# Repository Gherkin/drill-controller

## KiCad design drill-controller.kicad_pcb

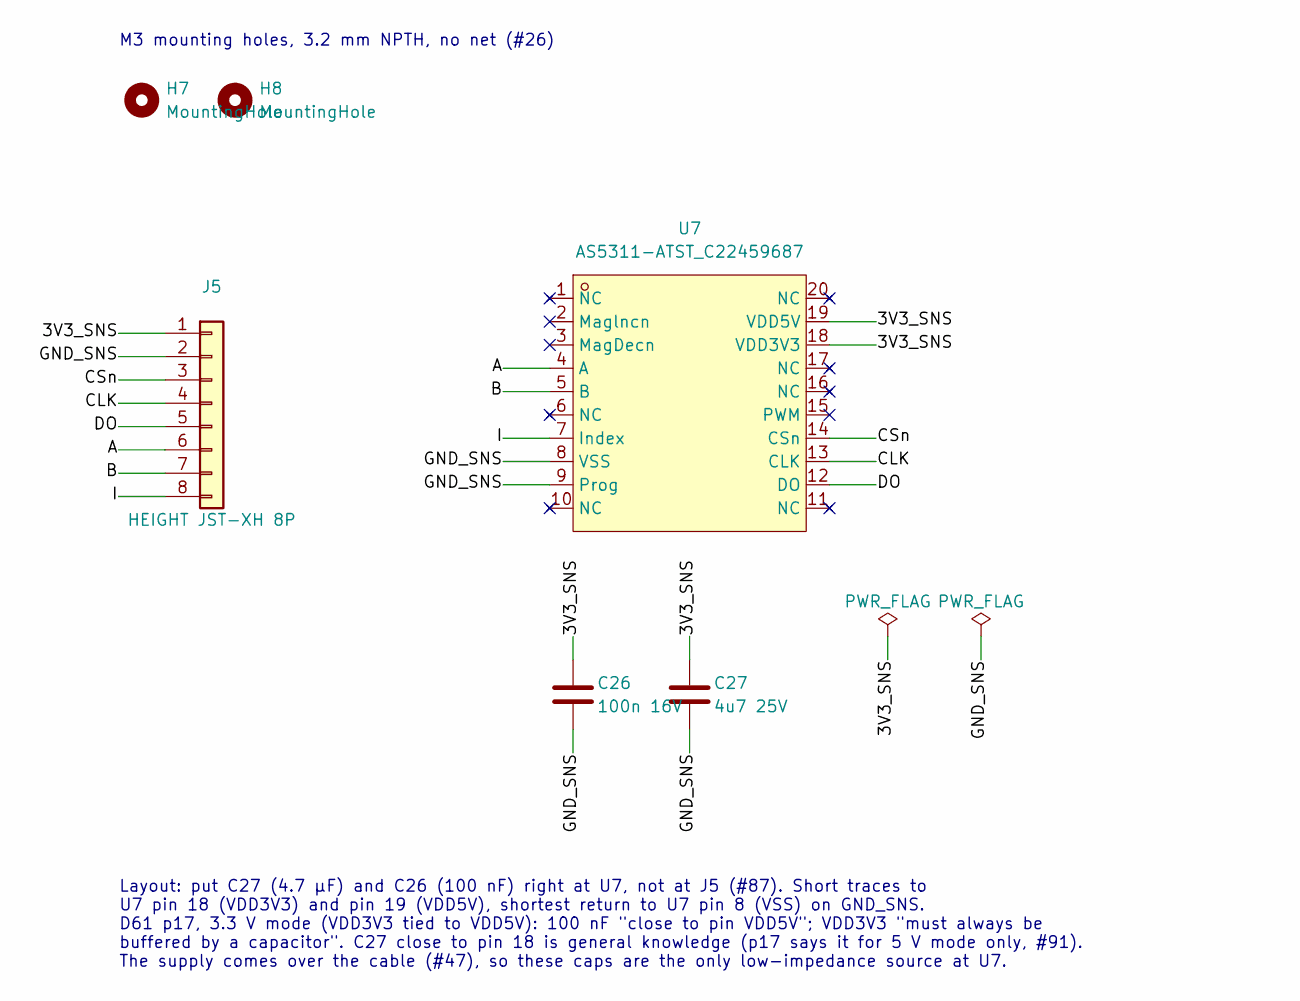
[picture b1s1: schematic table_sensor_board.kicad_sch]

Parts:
C26: 100n 16V; C_0402_1005Metric; LCSC Part C1525
C27: 4u7 25V; C_0805_2012Metric; LCSC Part C1779
H7, H8: MountingHole; MountingHole_3.2mm_M3_ISO14580
J5: HEIGHT JST-XH 8P; CONN-TH_8P-P2.50_B8B-XH-2-LF-SN; LCSC Part C157973
U7: AS5311-ATST_C22459687; TSSOP-20_L6.5-W4.4-P0.65-LS6.4-BL; LCSC Part C22459687

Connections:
/Table Height Sensor Board/3V3_SNS: C26.1, C27.1, J5.1, U7.18 (VDD3V3), U7.19 (VDD5V)
/Table Height Sensor Board/A: J5.6, U7.4 (A)
/Table Height Sensor Board/B: J5.7, U7.5 (B)
/Table Height Sensor Board/CLK: J5.4, U7.13 (CLK)
/Table Height Sensor Board/CSn: J5.3, U7.14 (CSn)
/Table Height Sensor Board/DO: J5.5, U7.12 (DO)
/Table Height Sensor Board/GND_SNS: C26.2, C27.2, J5.2, U7.8 (VSS), U7.9 (Prog)
/Table Height Sensor Board/I: J5.8, U7.7 (Index)

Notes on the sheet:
Layout: put C27 (4.7 µF) and C26 (100 nF) right at U7, not at J5 (#87). Short traces to U7 pin 18 (VDD3V3) and pin 19 (VDD5V), shortest return to U7 pin 8 (VSS) on GND_SNS. D61 p17, 3.3 V mode (VDD3V3 tied to VDD5V): 100 nF "close to pin VDD5V"; VDD3V3 "must always be buffered by a capacitor". C27 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
M3 mounting holes, 3.2 mm NPTH, no net (#26)

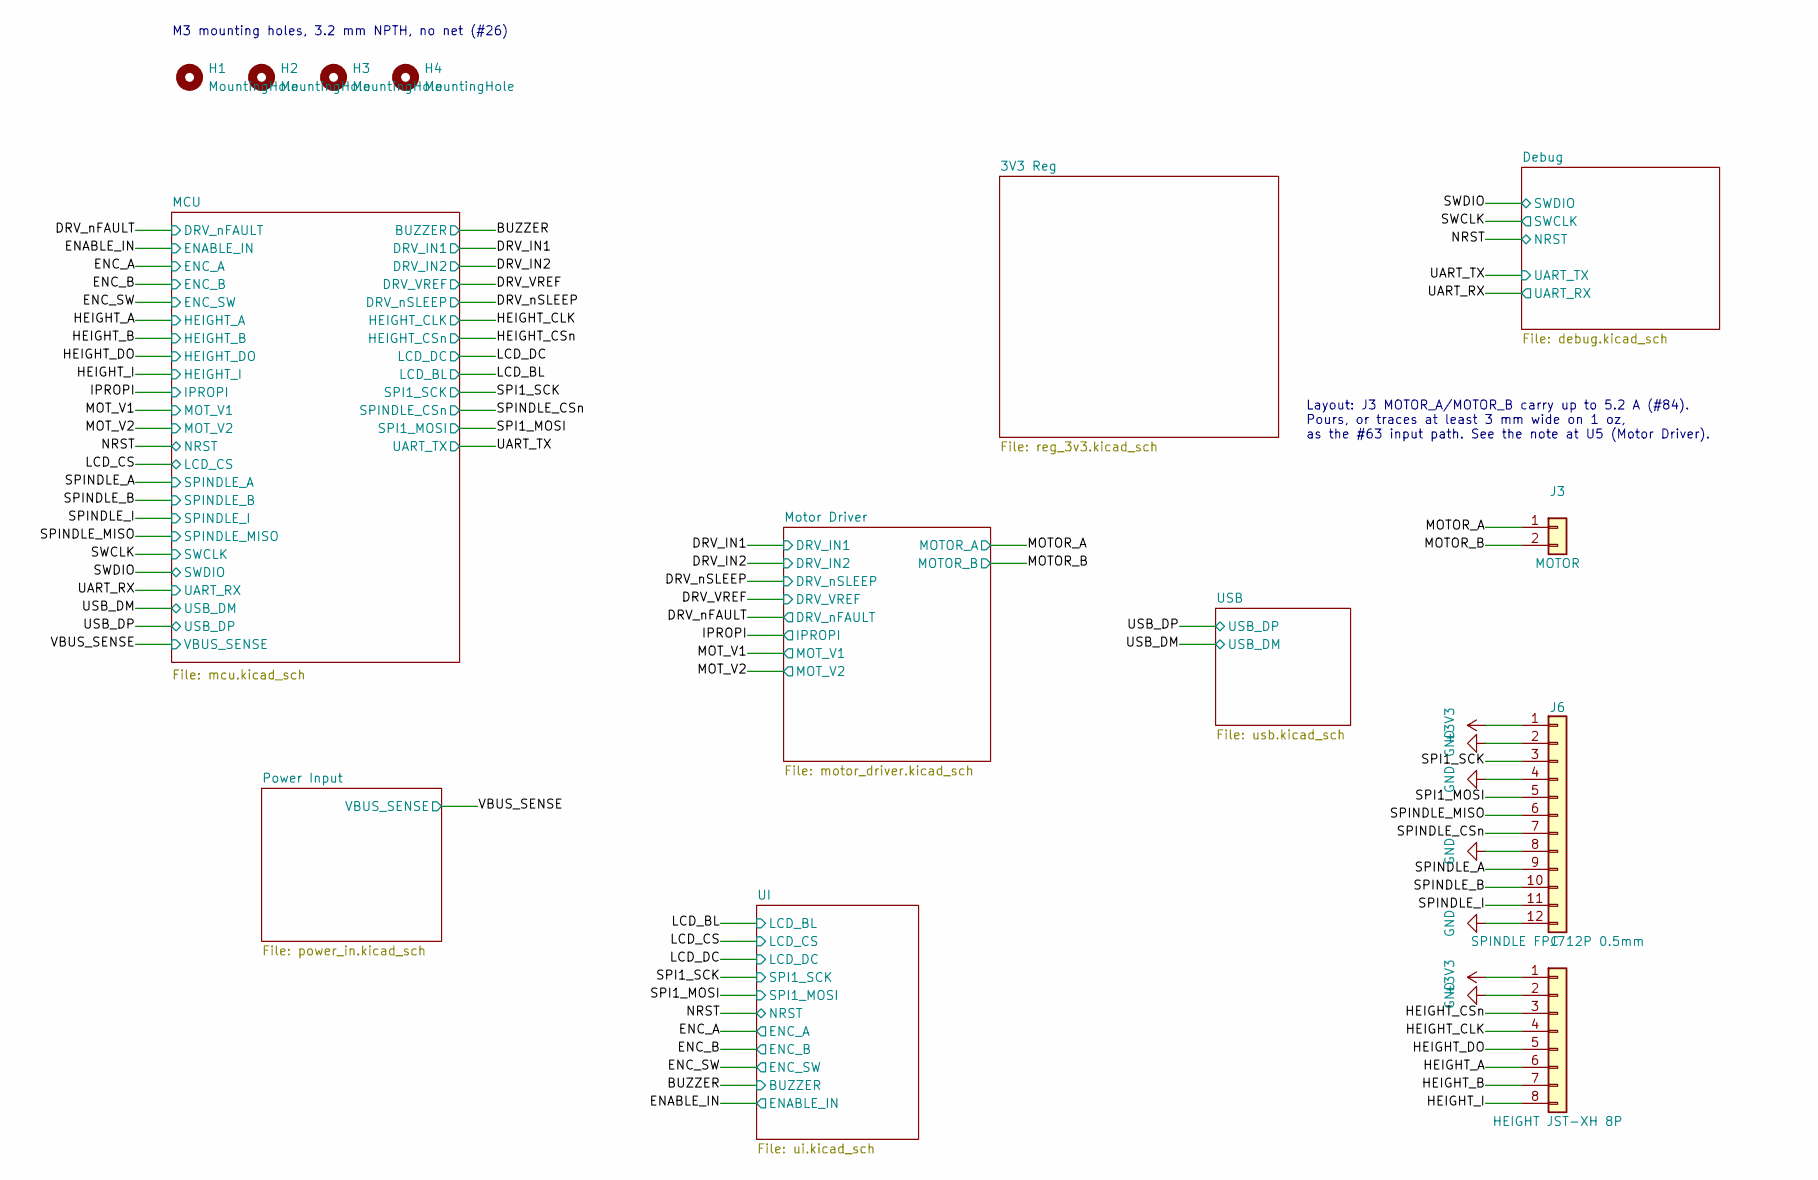
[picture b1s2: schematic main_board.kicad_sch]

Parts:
H1, H2, H3, H4: MountingHole; MountingHole_3.2mm_M3_ISO14580
J3: MOTOR; CONN-TH_XY128V-A-5.08-2P; LCSC Part C557665
J6: SPINDLE FPC 12P 0.5mm; FPC-SMD_12P-P0.50_HC-FPC-05-20-12RLTAG; LCSC Part C19270548
J7: HEIGHT JST-XH 8P; CONN-TH_8P-P2.50_B8B-XH-2-LF-SN; LCSC Part C157973

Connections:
+3V3: J6.1, J7.1; also elsewhere on the board
/Main Board/HEIGHT_A: J7.6; also elsewhere on the board
/Main Board/HEIGHT_B: J7.7; also elsewhere on the board
/Main Board/HEIGHT_CLK: J7.4; also elsewhere on the board
/Main Board/HEIGHT_CSn: J7.3; also elsewhere on the board
/Main Board/HEIGHT_DO: J7.5; also elsewhere on the board
/Main Board/HEIGHT_I: J7.8; also elsewhere on the board
/Main Board/MOTOR_A: J3.1; also elsewhere on the board
/Main Board/MOTOR_B: J3.2; also elsewhere on the board
/Main Board/SPI1_MOSI: J6.5; also elsewhere on the board
/Main Board/SPI1_SCK: J6.3; also elsewhere on the board
/Main Board/SPINDLE_A: J6.9; also elsewhere on the board
/Main Board/SPINDLE_B: J6.10; also elsewhere on the board
/Main Board/SPINDLE_CSn: J6.7; also elsewhere on the board
/Main Board/SPINDLE_I: J6.11; also elsewhere on the board
/Main Board/SPINDLE_MISO: J6.6; also elsewhere on the board
GND: J6.2, J6.4, J6.8, J6.12, J7.2; also elsewhere on the board

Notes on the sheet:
Layout: J3 MOTOR_A/MOTOR_B carry up to 5.2 A (#84). Pours, or traces at least 3 mm wide on 1 oz, as the #63 input path. See the note at U5 (Motor Driver).
M3 mounting holes, 3.2 mm NPTH, no net (#26)

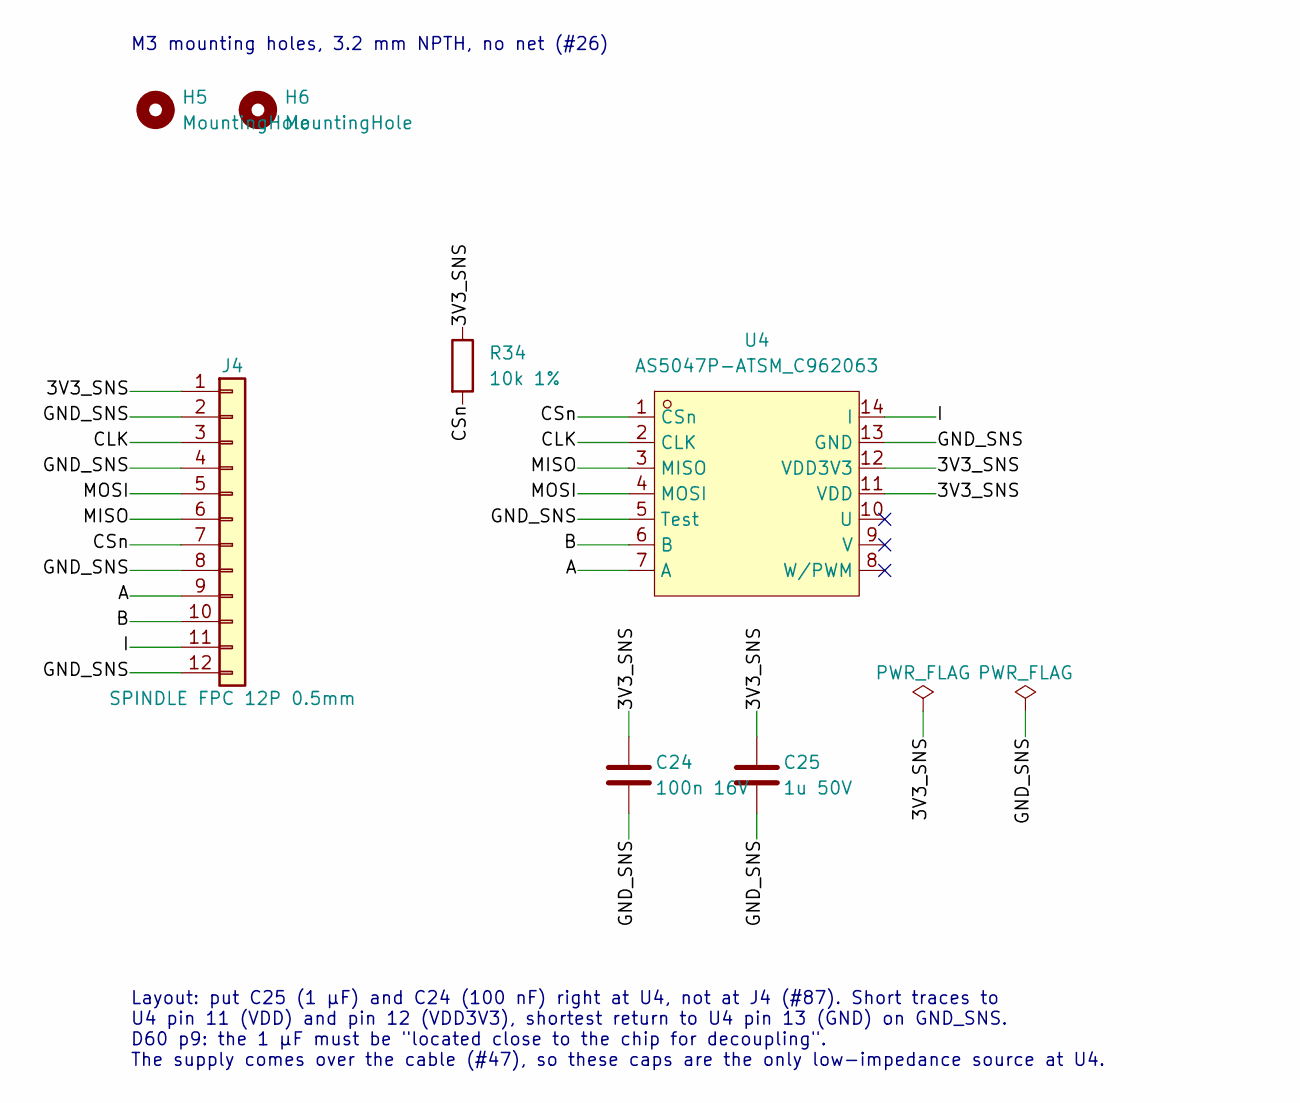
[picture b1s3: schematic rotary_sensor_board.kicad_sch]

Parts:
C24: 100n 16V; C_0402_1005Metric; LCSC Part C1525
C25: 1u 50V; C_0603_1608Metric; LCSC Part C15849
H5, H6: MountingHole; MountingHole_3.2mm_M3_ISO14580
J4: SPINDLE FPC 12P 0.5mm; FPC-SMD_12P-P0.50_HC-FPC-05-20-12RLTAG; LCSC Part C19270548
R34: 10k 1%; R_0402_1005Metric; LCSC Part C25744
U4: AS5047P-ATSM_C962063; TSSOP-14_L5.0-W4.4-P0.65-LS6.4-BL; LCSC Part C962063

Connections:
/Rotary Sensor Board/3V3_SNS: C24.1, C25.1, J4.1, R34.1, U4.11 (VDD), U4.12 (VDD3V3)
/Rotary Sensor Board/A: J4.9, U4.7 (A)
/Rotary Sensor Board/B: J4.10, U4.6 (B)
/Rotary Sensor Board/CLK: J4.3, U4.2 (CLK)
/Rotary Sensor Board/CSn: J4.7, R34.2, U4.1 (CSn)
/Rotary Sensor Board/GND_SNS: C24.2, C25.2, J4.2, J4.4, J4.8, J4.12, U4.5 (Test), U4.13 (GND)
/Rotary Sensor Board/I: J4.11, U4.14 (I)
/Rotary Sensor Board/MISO: J4.6, U4.3 (MISO)
/Rotary Sensor Board/MOSI: J4.5, U4.4 (MOSI)

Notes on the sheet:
M3 mounting holes, 3.2 mm NPTH, no net (#26)
Layout: put C25 (1 µF) and C24 (100 nF) right at U4, not at J4 (#87). Short traces to U4 pin 11 (VDD) and pin 12 (VDD3V3), shortest return to U4 pin 13 (GND) on GND_SNS. D60 p9: the 1 µF must be "located close to the chip for decoupling". The supply comes over the cable (#47), so these caps are the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

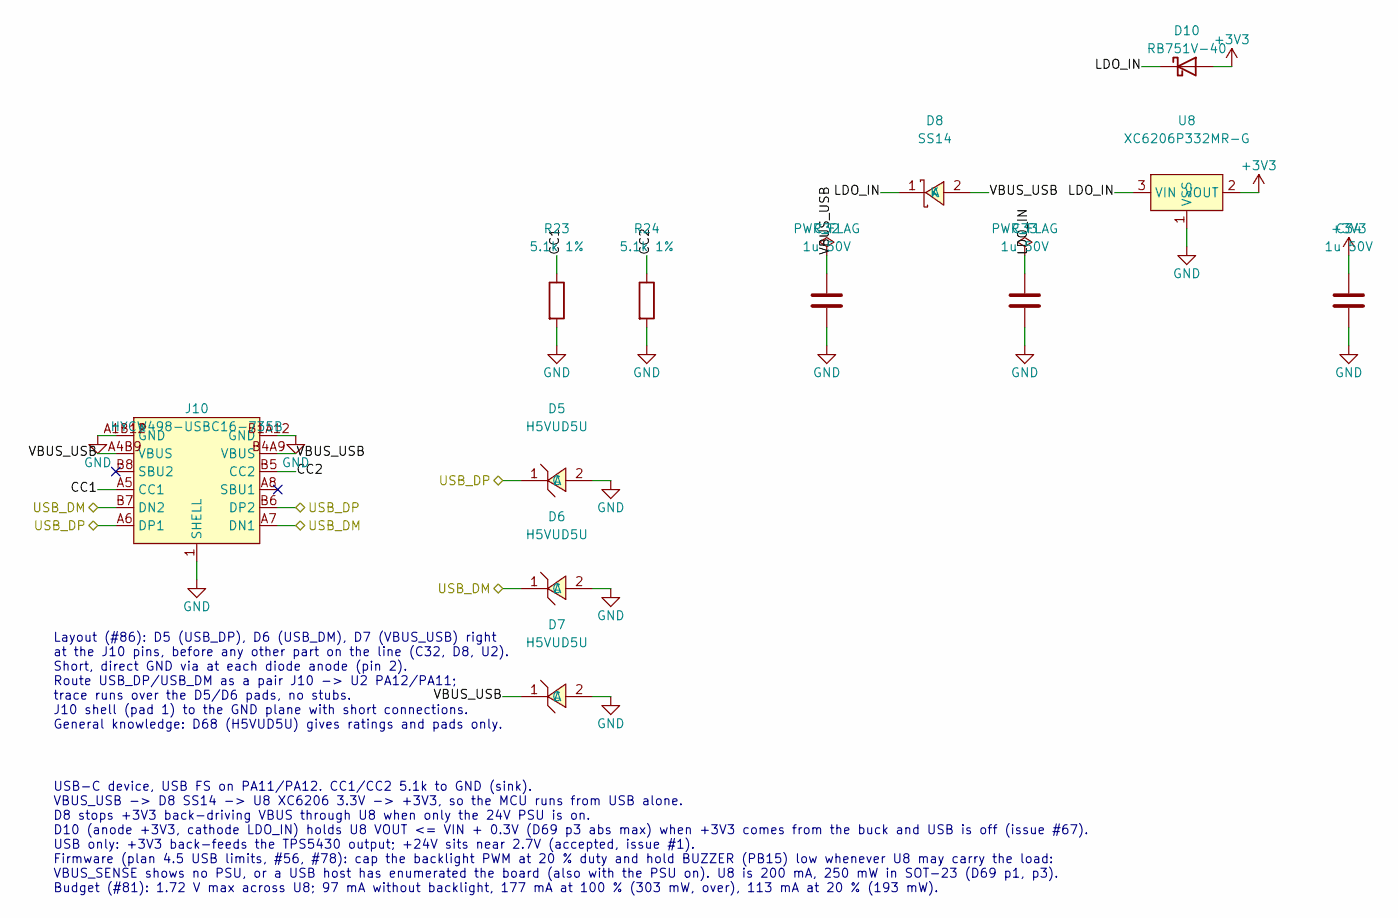
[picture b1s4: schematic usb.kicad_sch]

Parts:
C32, C33, C34: 1u 50V; C_0603_1608Metric; LCSC Part C15849
D5, D6, D7: H5VUD5U; SOD-523_L1.2-W0.8-LS1.6-RD; LCSC Part C20617921
D8: SS14; SMA_L4.2-W2.6-LS5.0-RD_1; LCSC Part C2480
D10: RB751V-40; D_SOD-323; LCSC Part C7502691
J10: HYCW498-USBC16-735B; USB-C-SMD_HYCW498-USBC16-735B; LCSC Part C42400252
R23, R24: 5.1k 1%; R_0402_1005Metric; LCSC Part C25905
U8: XC6206P332MR-G; SOT-23-3_L2.9-W1.6-P1.90-LS2.8-BR; LCSC Part C5446

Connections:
+3V3: C34.1, D10.2 (A), U8.2 (VOUT); also elsewhere on the board
/Main Board/USB/CC1: J10.A5 (CC1), R23.1
/Main Board/USB/CC2: J10.B5 (CC2), R24.1
/Main Board/USB/LDO_IN: C33.1, D8.1 (K), D10.1 (K), U8.3 (VIN)
/Main Board/USB/VBUS_USB: C32.1, D7.1 (C), D8.2 (A), J10.A4B9 (VBUS), J10.B4A9 (VBUS)
/Main Board/USB_DM: D6.1 (C), J10.A7 (DN1), J10.B7 (DN2); also elsewhere on the board
/Main Board/USB_DP: D5.1 (C), J10.A6 (DP1), J10.B6 (DP2); also elsewhere on the board
GND: C32.2, C33.2, C34.2, D5.2 (A), D6.2 (A), D7.2 (A), J10.1 (SHELL), J10.A1B12 (GND), J10.B1A12 (GND), R23.2, R24.2, U8.1 (VSS); also elsewhere on the board

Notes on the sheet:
Layout (#86): D5 (USB_DP), D6 (USB_DM), D7 (VBUS_USB) right at the J10 pins, before any other part on the line (C32, D8, U2). Short, direct GND via at each diode anode (pin 2). Route USB_DP/USB_DM as a pair J10 -> U2 PA12/PA11; trace runs over the D5/D6 pads, no stubs. J10 shell (pad 1) to the GND 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
USB-C device, USB FS on PA11/PA12. CC1/CC2 5.1k to GND (sink). VBUS_USB -> D8 SS14 -> U8 XC6206 3.3V -> +3V3, so the MCU runs from USB alone. D8 stops +3V3 back-driving VBUS through U8 when only the 24V PSU is on. D10 (anode +3V3, cathode LDO_IN) holds U8 VOUT <= VIN + 0.3V (D69 p3 abs max) when +3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

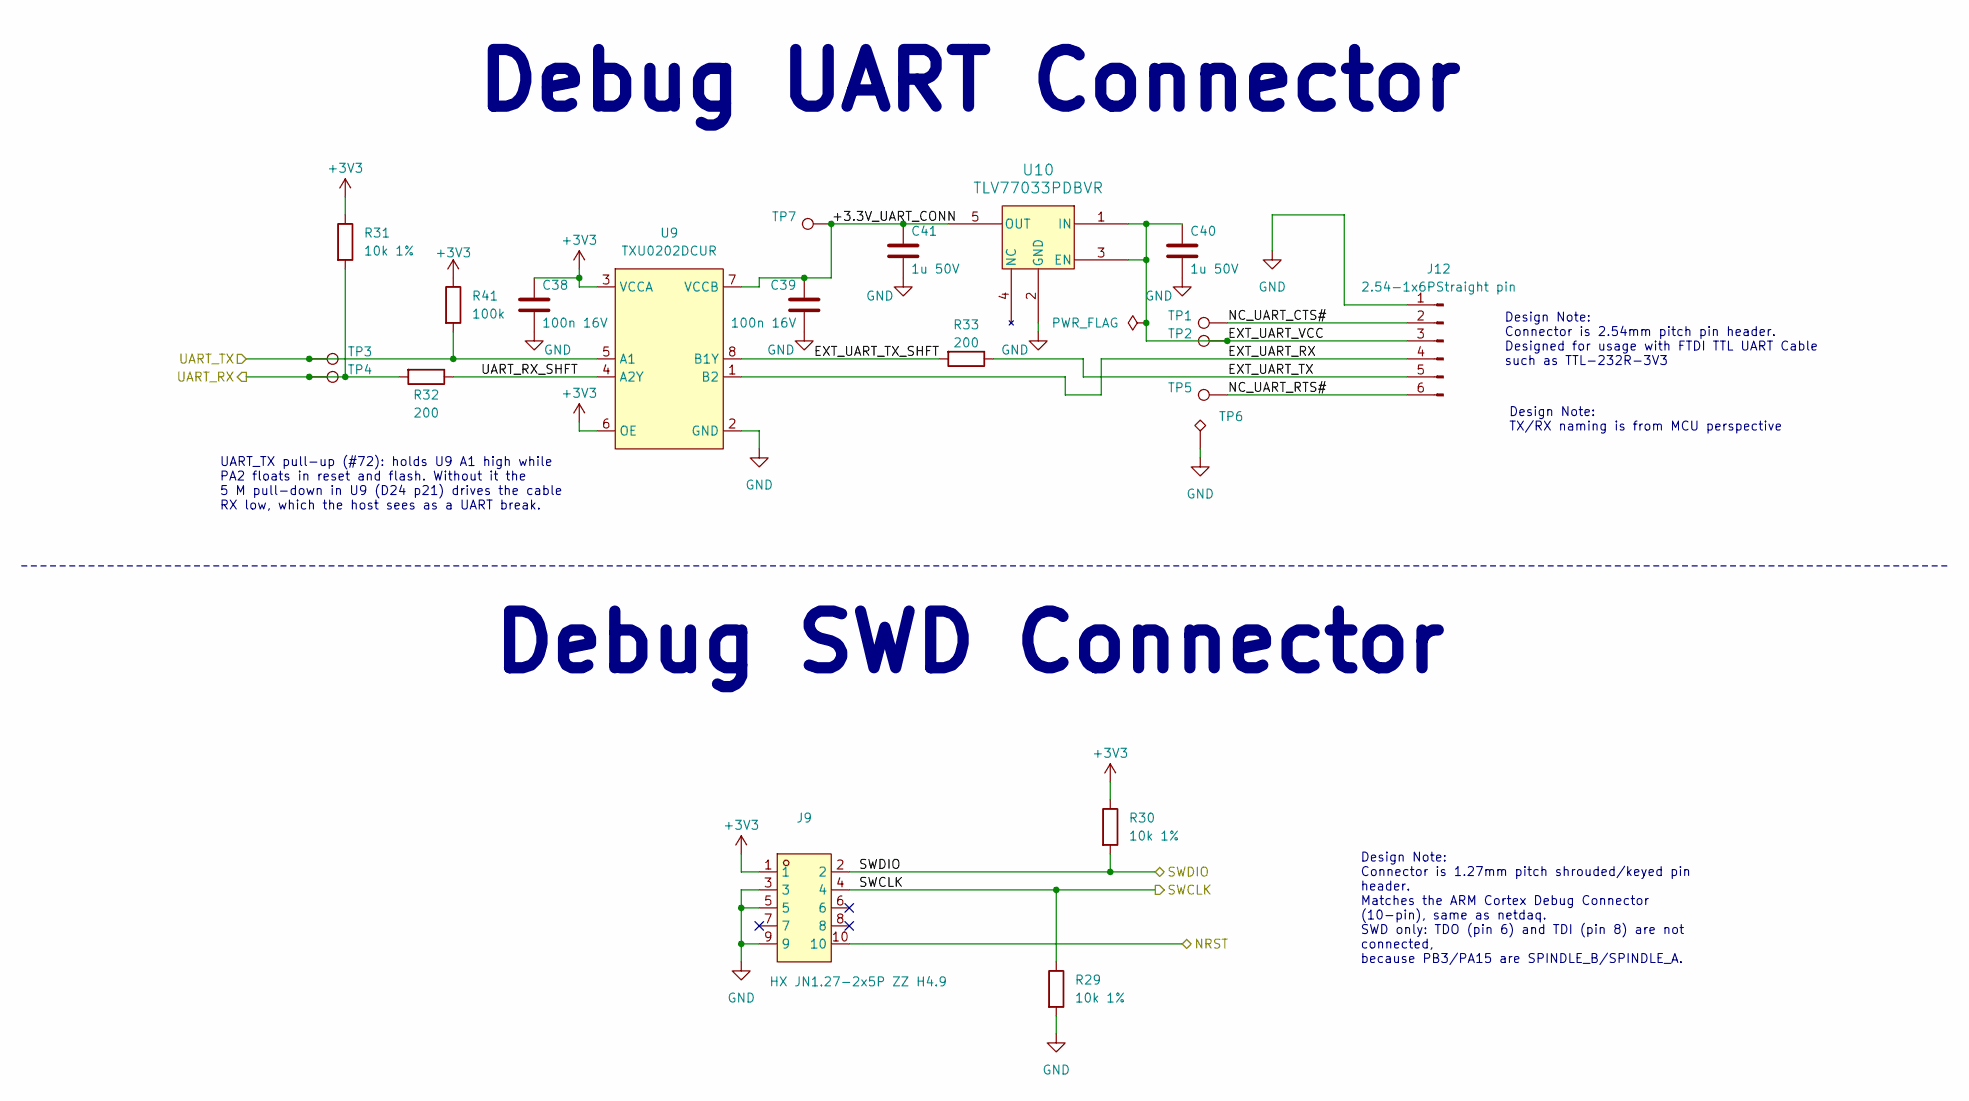
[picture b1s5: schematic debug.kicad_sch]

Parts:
C38, C39: 100n 16V; C_0402_1005Metric; Tolerance 10%; Voltage 16V; MPN CL05B104KO5NNNC; LCSC C1525
C40, C41: 1u 50V; C_0603_1608Metric; Tolerance 10%; Voltage 50V; MPN CL10A105KB8NNNC; LCSC C15849
J9: HX JN1.27-2x5P ZZ H4.9; CONN-TH_10P-P1.27_HX-JN1.27-2X5P-ZZ-H4.9; MPN HX JN1.27-2x5P ZZ H4.9; LCSC Part C42372547
J12: 2.54-1x6PStraight pin; PinHeader_1x06_P2.54mm_Vertical; MPN 2.54-1x6PStraight pin; LCSC Basic/Pref extended
R29, R30, R31: 10k 1%; R_0402_1005Metric; Tolerance 1%; Voltage 50V; MPN 0402WGF1002TCE; LCSC Basic/Pref basic
R32, R33: 200; R_0402_1005Metric; Tolerance 1%; Voltage 50V; MPN 0402WGF2000TCE; LCSC Basic/Pref basic
R41: 100k; R_0402_1005Metric; LCSC Part C25741
TP1, TP2, TP3, TP4, TP5, TP7: TestPoint; TestPoint_THTPad_D1.0mm_Drill0.5mm
TP6: TestPoint_Alt; TestPoint_THTPad_1.0x1.0mm_Drill0.5mm
U9: TXU0202DCUR; VSSOP-8_L2.3-W2.0-P0.50-LS3.1-BR; MPN TXU0202DCUR; LCSC Part C5186957
U10: TLV77033PDBVR; SOT-23-5_DBV_TEX; MPN TLV77033PDBVR; LCSC C36996065

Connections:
+3V3: C38.1, J9.1, R30.1, R31.1, R41.1, U9.3 (VCCA), U9.6 (OE); also elsewhere on the board
/Main Board/Debug/+3.3V_UART_CONN: C39.1, C41.1, TP7.1 (1_1), U9.7 (VCCB), U10.5 (OUT)
/Main Board/Debug/EXT_UART_RX: J12.4, U9.1 (B2)
/Main Board/Debug/EXT_UART_TX: J12.5, R33.1
/Main Board/Debug/EXT_UART_TX_SHFT: R33.2, U9.8 (B1Y)
/Main Board/Debug/EXT_UART_VCC: C40.1, J12.3, TP2.1 (1_1), U10.1 (IN), U10.3 (EN)
/Main Board/Debug/NC_UART_CTS#: J12.2, TP1.1 (1_1)
/Main Board/Debug/NC_UART_RTS#: J12.6, TP5.1 (1_1)
/Main Board/Debug/UART_RX_SHFT: R32.1, U9.4 (A2Y)
/Main Board/NRST: J9.10; also elsewhere on the board
/Main Board/SWCLK: J9.4, R29.1; also elsewhere on the board
/Main Board/SWDIO: J9.2, R30.2; also elsewhere on the board
/Main Board/UART_RX: R31.2, R32.2, TP4.1 (1_1); also elsewhere on the board
/Main Board/UART_TX: R41.2, TP3.1 (1_1), U9.5 (A1); also elsewhere on the board
GND: C38.2, C39.2, C40.2, C41.2, J9.3, J9.5, J9.9, J12.1, R29.2, TP6.1 (1_1), U9.2 (GND), U10.2 (GND); also elsewhere on the board

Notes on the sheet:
Debug UART Connector
UART_TX pull-up (#72): holds U9 A1 high while PA2 floats in reset and flash. Without it the 5 M pull-down in U9 (D24 p21) drives the cable RX low, which the host sees as a UART break.
Debug SWD Connector
Design Note: Connector is 1.27mm pitch shrouded/keyed pin header. Matches the ARM Cortex Debug Connector (10-pin), same as netdaq. SWD only: TDO (pin 6) and TDI (pin 8) are not connected, because PB3/PA15 are SPINDLE_B/SPINDLE_A.
Design Note: TX/RX naming is from MCU perspective
Design Note: Connector is 2.54mm pitch pin header. Designed for usage with FTDI TTL UART Cable such as TTL-232R-3V3

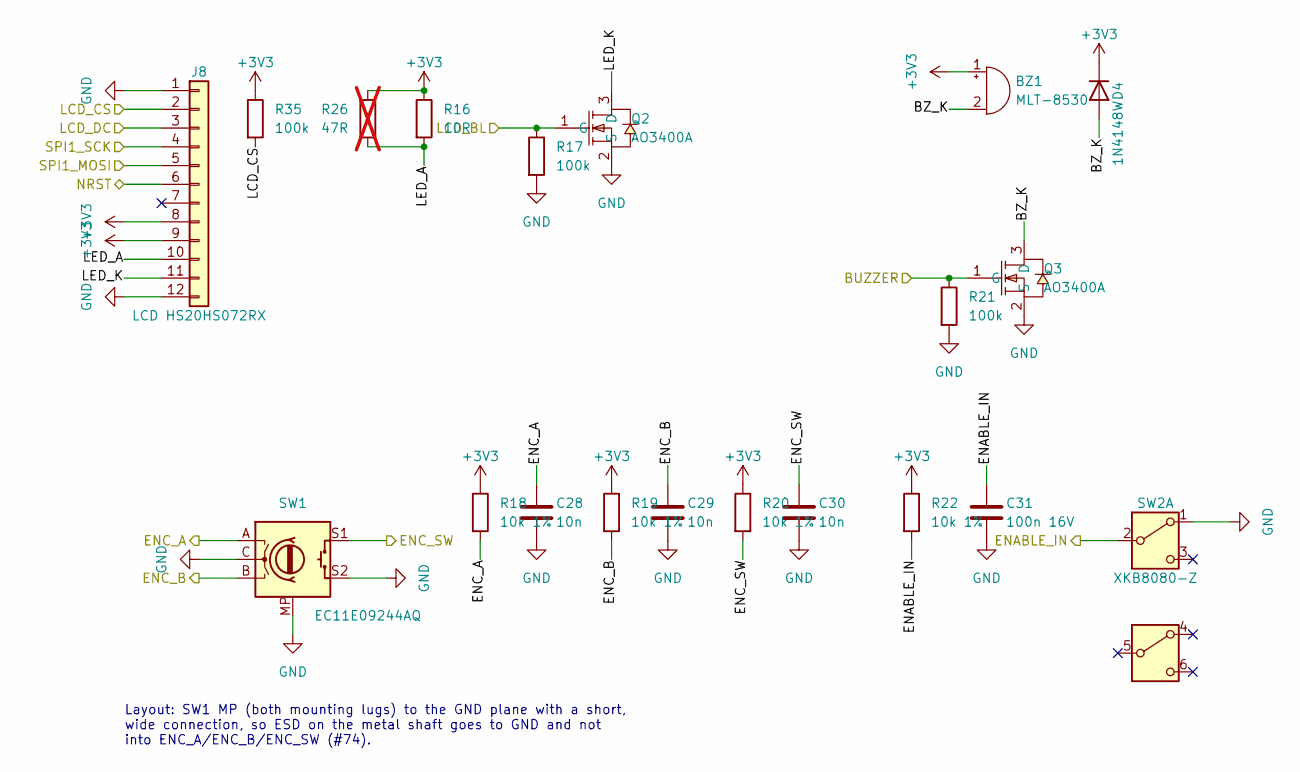
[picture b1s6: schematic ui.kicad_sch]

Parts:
BZ1: MLT-8530; BUZ-SMD_4P-L8.5-W8.5-P8.50-BR; LCSC Part C94599
C28, C29, C30: 10n; C_0402_1005Metric; LCSC Part C15195
C31: 100n 16V; C_0402_1005Metric; LCSC Part C1525
D4: 1N4148W; D_SOD-123; LCSC Part C81598
J8: LCD HS20HS072RX; FPC-SMD_12P-P0.50_HC-FPC-05-20-12RLTAG; LCSC Part C19270548
Q2, Q3: AO3400A; SOT-23-3_L2.9-W1.3-P1.90-LS2.4-BR; LCSC Part C20917
R16: 10R; R_0603_1608Metric; LCSC Part C22859
R17, R21, R35: 100k; R_0402_1005Metric; LCSC Part C25741
R18, R19, R20, R22: 10k 1%; R_0402_1005Metric; LCSC Part C25744
R26: 47R; R_0603_1608Metric; LCSC Part C23182; not fitted
SW1: EC11E09244AQ; RotaryEncoder_Alps_EC11E-Switch_Vertical_H20mm; LCSC Part C470753
SW2: XKB8080-Z; SW-TH_6P-L8.0-W8.0-P2.50; LCSC Part C318860

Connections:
+3V3: BZ1.1 (+), D4.1 (K), J8.8, J8.9, R16.1, R18.1, R19.1, R20.1, R22.1, R26.1, R35.1; also elsewhere on the board
/Main Board/BUZZER: Q3.1 (G), R21.1; also elsewhere on the board
/Main Board/ENABLE_IN: C31.1, R22.2, SW2.2 (B); also elsewhere on the board
/Main Board/ENC_A: C28.1, R18.2, SW1.A; also elsewhere on the board
/Main Board/ENC_B: C29.1, R19.2, SW1.B; also elsewhere on the board
/Main Board/ENC_SW: C30.1, R20.2, SW1.S1; also elsewhere on the board
/Main Board/LCD_BL: Q2.1 (G), R17.1; also elsewhere on the board
/Main Board/LCD_CS: J8.2, R35.2; also elsewhere on the board
/Main Board/LCD_DC: J8.3; also elsewhere on the board
/Main Board/NRST: J8.6; also elsewhere on the board
/Main Board/SPI1_MOSI: J8.5; also elsewhere on the board
/Main Board/SPI1_SCK: J8.4; also elsewhere on the board
/Main Board/UI/BZ_K: BZ1.2 (-), D4.2 (A), Q3.3 (D)
/Main Board/UI/LED_A: J8.10, R16.2, R26.2
/Main Board/UI/LED_K: J8.11, Q2.3 (D)
GND: C28.2, C29.2, C30.2, C31.2, J8.1, J8.12, Q2.2 (S), Q3.2 (S), R17.2, R21.2, SW1.C, SW1.MP, SW1.S2, SW2.1 (A); also elsewhere on the board

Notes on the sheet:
Layout: SW1 MP (both mounting lugs) to the GND plane with a short, wide connection, so ESD on the metal shaft goes to GND and not into ENC_A/ENC_B/ENC_SW (#74).

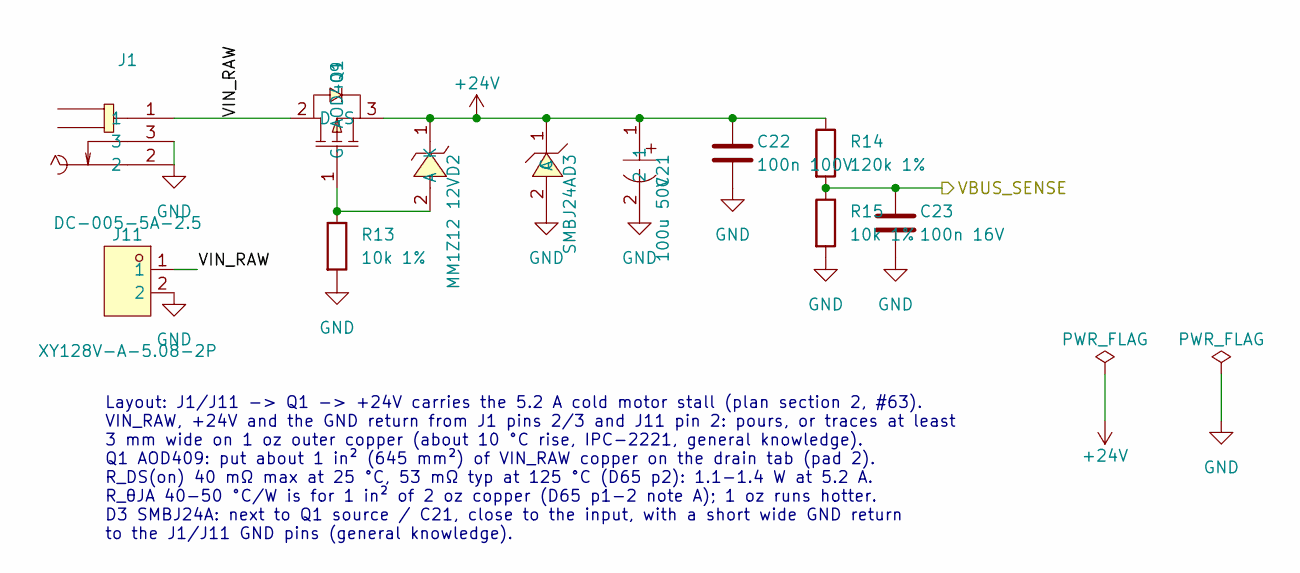
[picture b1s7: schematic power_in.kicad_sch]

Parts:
C21: 100u 50V; CAP-SMD_BD6.3-L6.6-W6.6-LS7.6-RD; LCSC Part C3151829
C22: 100n 100V; C_0805_2012Metric; LCSC Part C28233
C23: 100n 16V; C_0402_1005Metric; LCSC Part C1525
D2: MM1Z12 12V; SOD-123_L2.7-W1.6-LS3.7-RD; LCSC Part C22379459
D3: SMBJ24A; SMB_L4.6-W3.6-LS5.3-RD; LCSC Part C353373
J1: DC-005-5A-2.5; DC-IN-TH_DC-005-5A-2.5; LCSC Part C381115
J11: XY128V-A-5.08-2P; CONN-TH_XY128V-A-5.08-2P; LCSC Part C557665
Q1: AOD409; TO-252-2_L6.6-W6.1-P4.57-LS9.9-TL-CW; LCSC Part C36220
R13, R15: 10k 1%; R_0402_1005Metric; LCSC Part C25744
R14: 120k 1%; R_0402_1005Metric; LCSC Part C25750

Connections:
+24V: C21.1, C22.1, D2.1 (K), D3.1 (C), Q1.3 (S), R14.1; also elsewhere on the board
/Main Board/Power Input/VIN_RAW: J1.1, J11.1, Q1.2 (D)
/Main Board/VBUS_SENSE: C23.1, R14.2, R15.1; also elsewhere on the board
GND: C21.2, C22.2, C23.2, D3.2 (A), J1.2, J1.3, J11.2, R13.2, R15.2; also elsewhere on the board
unnamed: D2.2 (A), Q1.1 (G), R13.1

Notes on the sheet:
Layout: J1/J11 -> Q1 -> +24V carries the 5.2 A cold motor stall (plan section 2, #63). VIN_RAW, +24V and the GND return from J1 pins 2/3 and J11 pin 2: pours, or traces at least 3 mm wide on 1 oz outer copper (about 10 °C rise, IPC-2221, general knowledge). Q1 AOD409: put about 1 in² (645 mm²) of V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

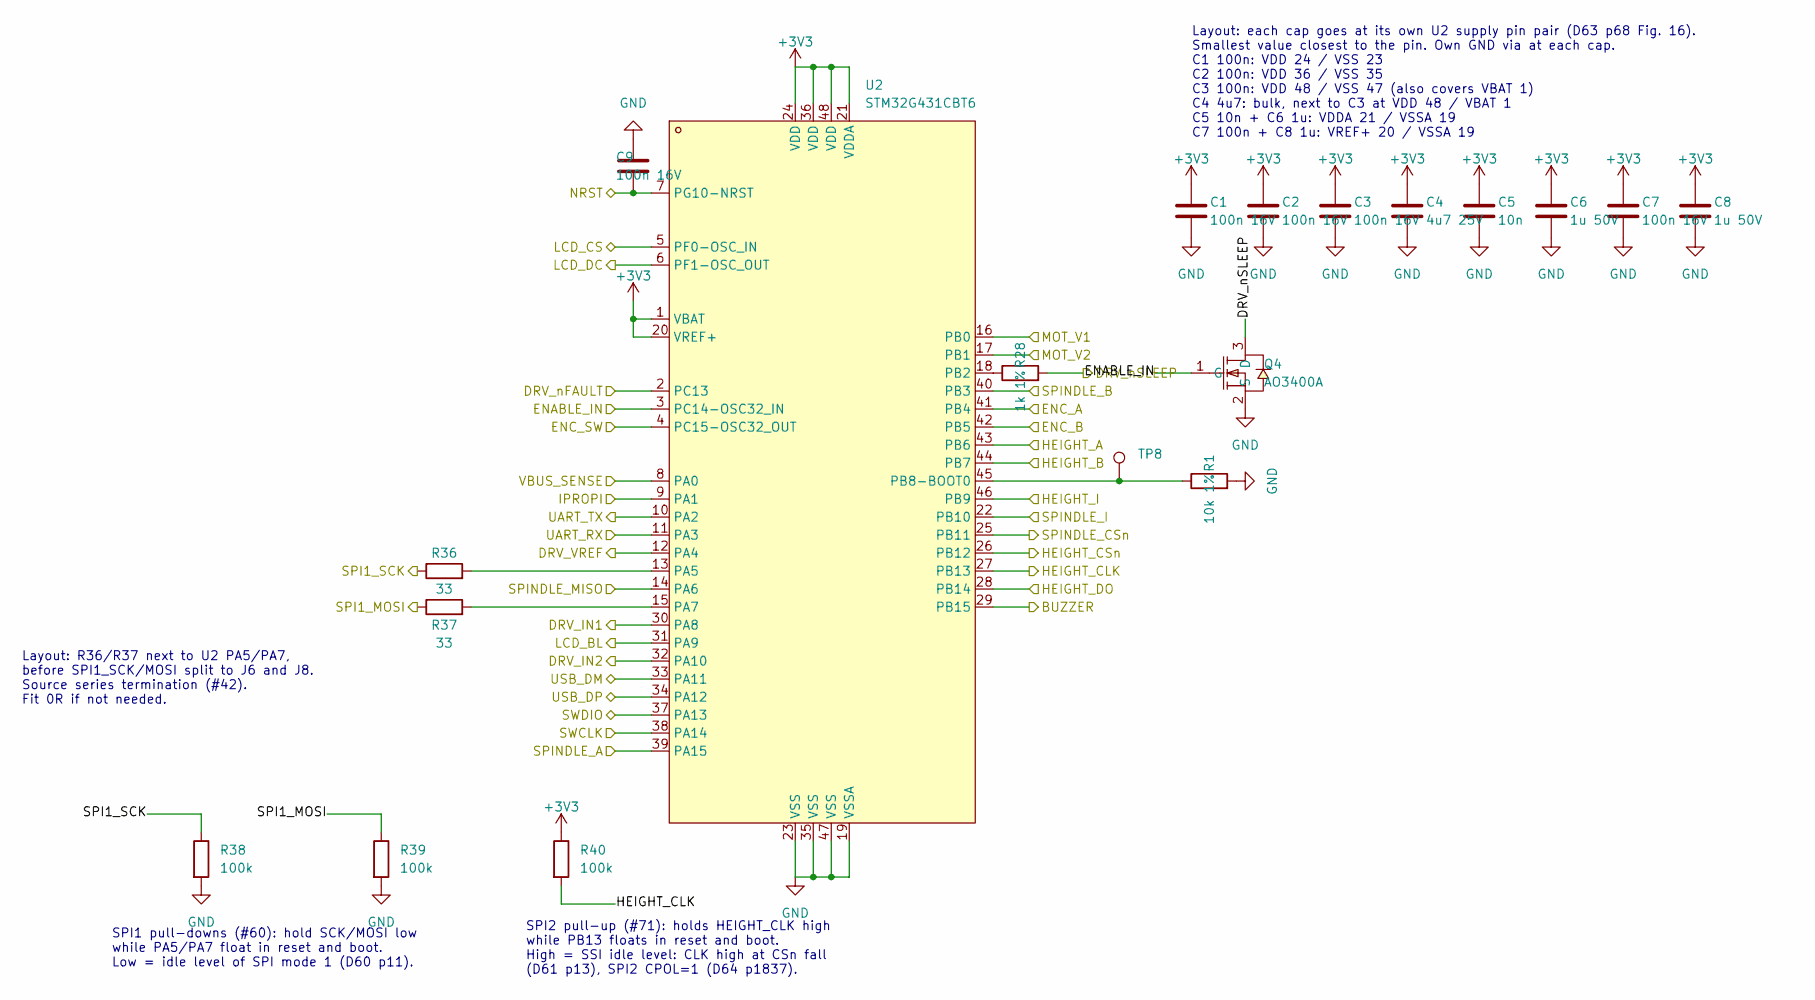
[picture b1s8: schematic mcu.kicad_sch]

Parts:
C1, C2, C3, C7, C9: 100n 16V; C_0402_1005Metric; LCSC Part C1525
C4: 4u7 25V; C_0805_2012Metric; LCSC Part C1779
C5: 10n; C_0402_1005Metric; LCSC Part C15195
C6, C8: 1u 50V; C_0603_1608Metric; LCSC Part C15849
Q4: AO3400A; SOT-23-3_L2.9-W1.3-P1.90-LS2.4-BR; LCSC Part C20917
R1: 10k 1%; R_0402_1005Metric; LCSC Part C25744
R28: 1k 1%; R_0402_1005Metric; LCSC Part C11702
R36, R37: 33; R_0402_1005Metric; LCSC Part C25105
R38, R39, R40: 100k; R_0402_1005Metric; LCSC Part C25741
TP8: TestPoint; TestPoint_THTPad_D1.0mm_Drill0.5mm
U2: STM32G431CBT6; LQFP-48_L7.0-W7.0-P0.50-LS9.0-BL; LCSC Part C529355

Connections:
+3V3: C1.1, C2.1, C3.1, C4.1, C5.1, C6.1, C7.1, C8.1, R40.1, U2.1 (VBAT), U2.20 (VREF+), U2.21 (VDDA), U2.24 (VDD), U2.36 (VDD), U2.48 (VDD); also elsewhere on the board
/Main Board/BUZZER: U2.29 (PB15); also elsewhere on the board
/Main Board/DRV_IN1: U2.30 (PA8); also elsewhere on the board
/Main Board/DRV_IN2: U2.32 (PA10); also elsewhere on the board
/Main Board/DRV_VREF: U2.12 (PA4); also elsewhere on the board
/Main Board/DRV_nFAULT: U2.2 (PC13); also elsewhere on the board
/Main Board/DRV_nSLEEP: Q4.3 (D), R28.2; also elsewhere on the board
/Main Board/ENABLE_IN: Q4.1 (G), U2.3 (PC14-OSC32_IN); also elsewhere on the board
/Main Board/ENC_A: U2.41 (PB4); also elsewhere on the board
/Main Board/ENC_B: U2.42 (PB5); also elsewhere on the board
/Main Board/ENC_SW: U2.4 (PC15-OSC32_OUT); also elsewhere on the board
/Main Board/HEIGHT_A: U2.43 (PB6); also elsewhere on the board
/Main Board/HEIGHT_B: U2.44 (PB7); also elsewhere on the board
/Main Board/HEIGHT_CLK: R40.2, U2.27 (PB13); also elsewhere on the board
/Main Board/HEIGHT_CSn: U2.26 (PB12); also elsewhere on the board
/Main Board/HEIGHT_DO: U2.28 (PB14); also elsewhere on the board
/Main Board/HEIGHT_I: U2.46 (PB9); also elsewhere on the board
/Main Board/IPROPI: U2.9 (PA1); also elsewhere on the board
/Main Board/LCD_BL: U2.31 (PA9); also elsewhere on the board
/Main Board/LCD_CS: U2.5 (PF0-OSC_IN); also elsewhere on the board
/Main Board/LCD_DC: U2.6 (PF1-OSC_OUT); also elsewhere on the board
/Main Board/MOT_V1: U2.16 (PB0); also elsewhere on the board
/Main Board/MOT_V2: U2.17 (PB1); also elsewhere on the board
/Main Board/NRST: C9.1, U2.7 (PG10-NRST); also elsewhere on the board
/Main Board/SPI1_MOSI: R37.1, R39.1; also elsewhere on the board
/Main Board/SPI1_SCK: R36.1, R38.1; also elsewhere on the board
/Main Board/SPINDLE_A: U2.39 (PA15); also elsewhere on the board
/Main Board/SPINDLE_B: U2.40 (PB3); also elsewhere on the board
/Main Board/SPINDLE_CSn: U2.25 (PB11); also elsewhere on the board
/Main Board/SPINDLE_I: U2.22 (PB10); also elsewhere on the board
/Main Board/SPINDLE_MISO: U2.14 (PA6); also elsewhere on the board
/Main Board/SWCLK: U2.38 (PA14); also elsewhere on the board
/Main Board/SWDIO: U2.37 (PA13); also elsewhere on the board
/Main Board/UART_RX: U2.11 (PA3); also elsewhere on the board
/Main Board/UART_TX: U2.10 (PA2); also elsewhere on the board
/Main Board/USB_DM: U2.33 (PA11); also elsewhere on the board
/Main Board/USB_DP: U2.34 (PA12); also elsewhere on the board
/Main Board/VBUS_SENSE: U2.8 (PA0); also elsewhere on the board
GND: C1.2, C2.2, C3.2, C4.2, C5.2, C6.2, C7.2, C8.2, C9.2, Q4.2 (S), R1.2, R38.2, R39.2, U2.19 (VSSA), U2.23 (VSS), U2.35 (VSS), U2.47 (VSS); also elsewhere on the board
unnamed: R36.2, U2.13 (PA5)
unnamed: R37.2, U2.15 (PA7)
unnamed: R28.1, U2.18 (PB2)
unnamed: R1.1, TP8.1 (1_1), U2.45 (PB8-BOOT0)

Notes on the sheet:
Layout: each cap goes at its own U2 supply pin pair (D63 p68 Fig. 16). Smallest value closest to the pin. Own GND via at each cap. C1 100n: VDD 24 / VSS 23 C2 100n: VDD 36 / VSS 35 C3 100n: VDD 48 / VSS 47 (also covers VBAT 1) C4 4u7: bulk, next to C3 at VDD 48 / VBAT 1 C5 10n + C6 1u: VDDA 21 / VS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
SPI1 pull-downs (#60): hold SCK/MOSI low while PA5/PA7 float in reset and boot. Low = idle level of SPI mode 1 (D60 p11).
SPI2 pull-up (#71): holds HEIGHT_CLK high while PB13 floats in reset and boot. High = SSI idle level: CLK high at CSn fall (D61 p13), SPI2 CPOL=1 (D64 p1837).
Layout: R36/R37 next to U2 PA5/PA7, before SPI1_SCK/MOSI split to J6 and J8. Source series termination (#42). Fit 0R if not needed.

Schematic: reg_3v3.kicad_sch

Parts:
C15: 10u 50V; C_1206_3216Metric; LCSC Part C13585
C16: 10n; C_0402_1005Metric; LCSC Part C15195
C17, C35, C36: 47u 10V; C_1206_3216Metric; LCSC Part C96123
C18: 1n; C_0402_1005Metric; LCSC Part C1523
C19: 150p; C_0402_1005Metric; LCSC Part C1527
C20: 100n 16V; C_0402_1005Metric; LCSC Part C1525
C37: 470p; C_0402_1005Metric; LCSC Part C1537
D1: SS34 40V 3A; D_SMA; LCSC Part C8678
L1: 15u; L_Sunlord_SWPA4020S; LCSC Part C36407
R10: 10k 1%; R_0402_1005Metric; LCSC Part C25744
R11: 5.1k 1%; R_0402_1005Metric; LCSC Part C25905
R12: 510 1%; R_0402_1005Metric; LCSC Part C25123
R27: 1.2k 1%; R_0402_1005Metric; LCSC Part C25862
TP9, TP10, TP11, TP12: TestPoint; TestPoint_THTPad_D1.0mm_Drill0.5mm
U1: TPS5430DDAR; ESOP-8_L4.9-W3.9-P1.27-LS6.0-TL-EP; LCSC Part C9864

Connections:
+3V3: C17.1, C18.1, C35.1, C36.1, C37.1, L1.1, R10.1, TP10.1 (1_1); also elsewhere on the board
+24V: C15.1, TP9.1 (1_1), U1.7 (VIN); also elsewhere on the board
/Main Board/3V3 Reg/BOOT: C16.1, U1.1 (BOOT)
/Main Board/3V3 Reg/SW: C16.2, D1.1 (K), L1.2, TP11.1 (1_1), U1.8 (PH)
/Main Board/3V3 Reg/VSNS: C18.2, C19.1, C20.1, C37.2, R10.2, R11.1, U1.4 (VSENSE)
GND: C15.2, C17.2, C19.2, C35.2, C36.2, D1.2 (A), R12.2, R27.2, TP12.1 (1_1), U1.6 (GND), U1.9 (PowerPAD); also elsewhere on the board
unnamed: C20.2, R12.1
unnamed: R11.2, R27.1

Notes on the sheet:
Layout: VSNS trace from the R10/R11/R27 divider to U1 VSENSE (pin 4): keep it away from the SW node (U1 PH, D1, L1). Route it under the output caps or on another layer (D59 p23-24, #63).
Layout: C15 10u X5R as close as possible to U1 VIN (pin 7). Small loop C15 - VIN - GND (pin 6 / PowerPAD): extend the top GND area from under U1 next to the VIN trace (D59 p23, #35).
Layout: keep the buck switching loops small (D59 p23-24, #63). D1 SS34 close to U1 PH (pin 8) and the U1 GND area: loop PH - D1 - GND - C15 as small as possible. L1 very close to U1 PH; keep the SW copper (PH, D1, L1, C16) small. C16 (boot cap) close to U1 BOOT (pin 1) and PH, short traces. Output 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
Layout: TP9-TP12 are bring-up test pads, not fitted (#36). TP11 (SW): put it on the U1 PH / L1 copper with no stub; keep the SW area small. TP12 (GND): next to C15 / U1 GND, as the scope ground for TP9-TP11.
